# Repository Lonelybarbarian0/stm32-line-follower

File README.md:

# stm32-line-follower
An advanced line follower based on STM32F446RE. This design consists of 12 Analog IR sensors (CNY70) , a dual H-bridge driver (TB6612FNG) , has I2C ports for oled display , push buttons , 12V battery accomodation , SWD , and debug UART ports for programming and debugging the microcontroller.
Has two voltage regulators for 3V3 and 5V.

It has mounting holes for caster wheel (15mm) , specifically this one: https://robu.in/product/mini-3pi-car-n20-caster-robot-ball-wheel/?gad_source=1&gad_campaignid=20387462343&gbraid=0AAAAADvLFWdYTelDnTxbAqraLI1H4bepI&gclid=Cj0KCQjwm93DBhD_ARIsADR_DjHucWRJYjZKFOhlfUYJuclHHiB9VbRIZePeRFHvk6mzUTXiPl632kYaAhp5EALw_wcB

It also has mounting holes for adding both N20 (18mm) as well as 14mm * 16mm motor brackets like:https://roboticsdna.in/product/25mm-dc-gear-motor-block-l-shape-motor-bracket/?src=google&kwd=&adgroup={adgroup}&device=c&campaign={campaign}&adgroup={adgroup}&keyword=&matchtype=&gad_source=1&gad_campaignid=22793537991&gbraid=0AAAAAC-xzeH1j9IDTkCSxU-zOjWUDu6ZW&gclid=Cj0KCQjwm93DBhD_ARIsADR_DjG1hGDh40R1bVBjp1YW7XD5IBcDVYip5r4QT6sreYXs5M1MaoTtmnkaAhj5EALw_wcB

Features power on led , a power on switch etc...

SIDE VIEW:

BACK VIEW:

PIN CONFIG:

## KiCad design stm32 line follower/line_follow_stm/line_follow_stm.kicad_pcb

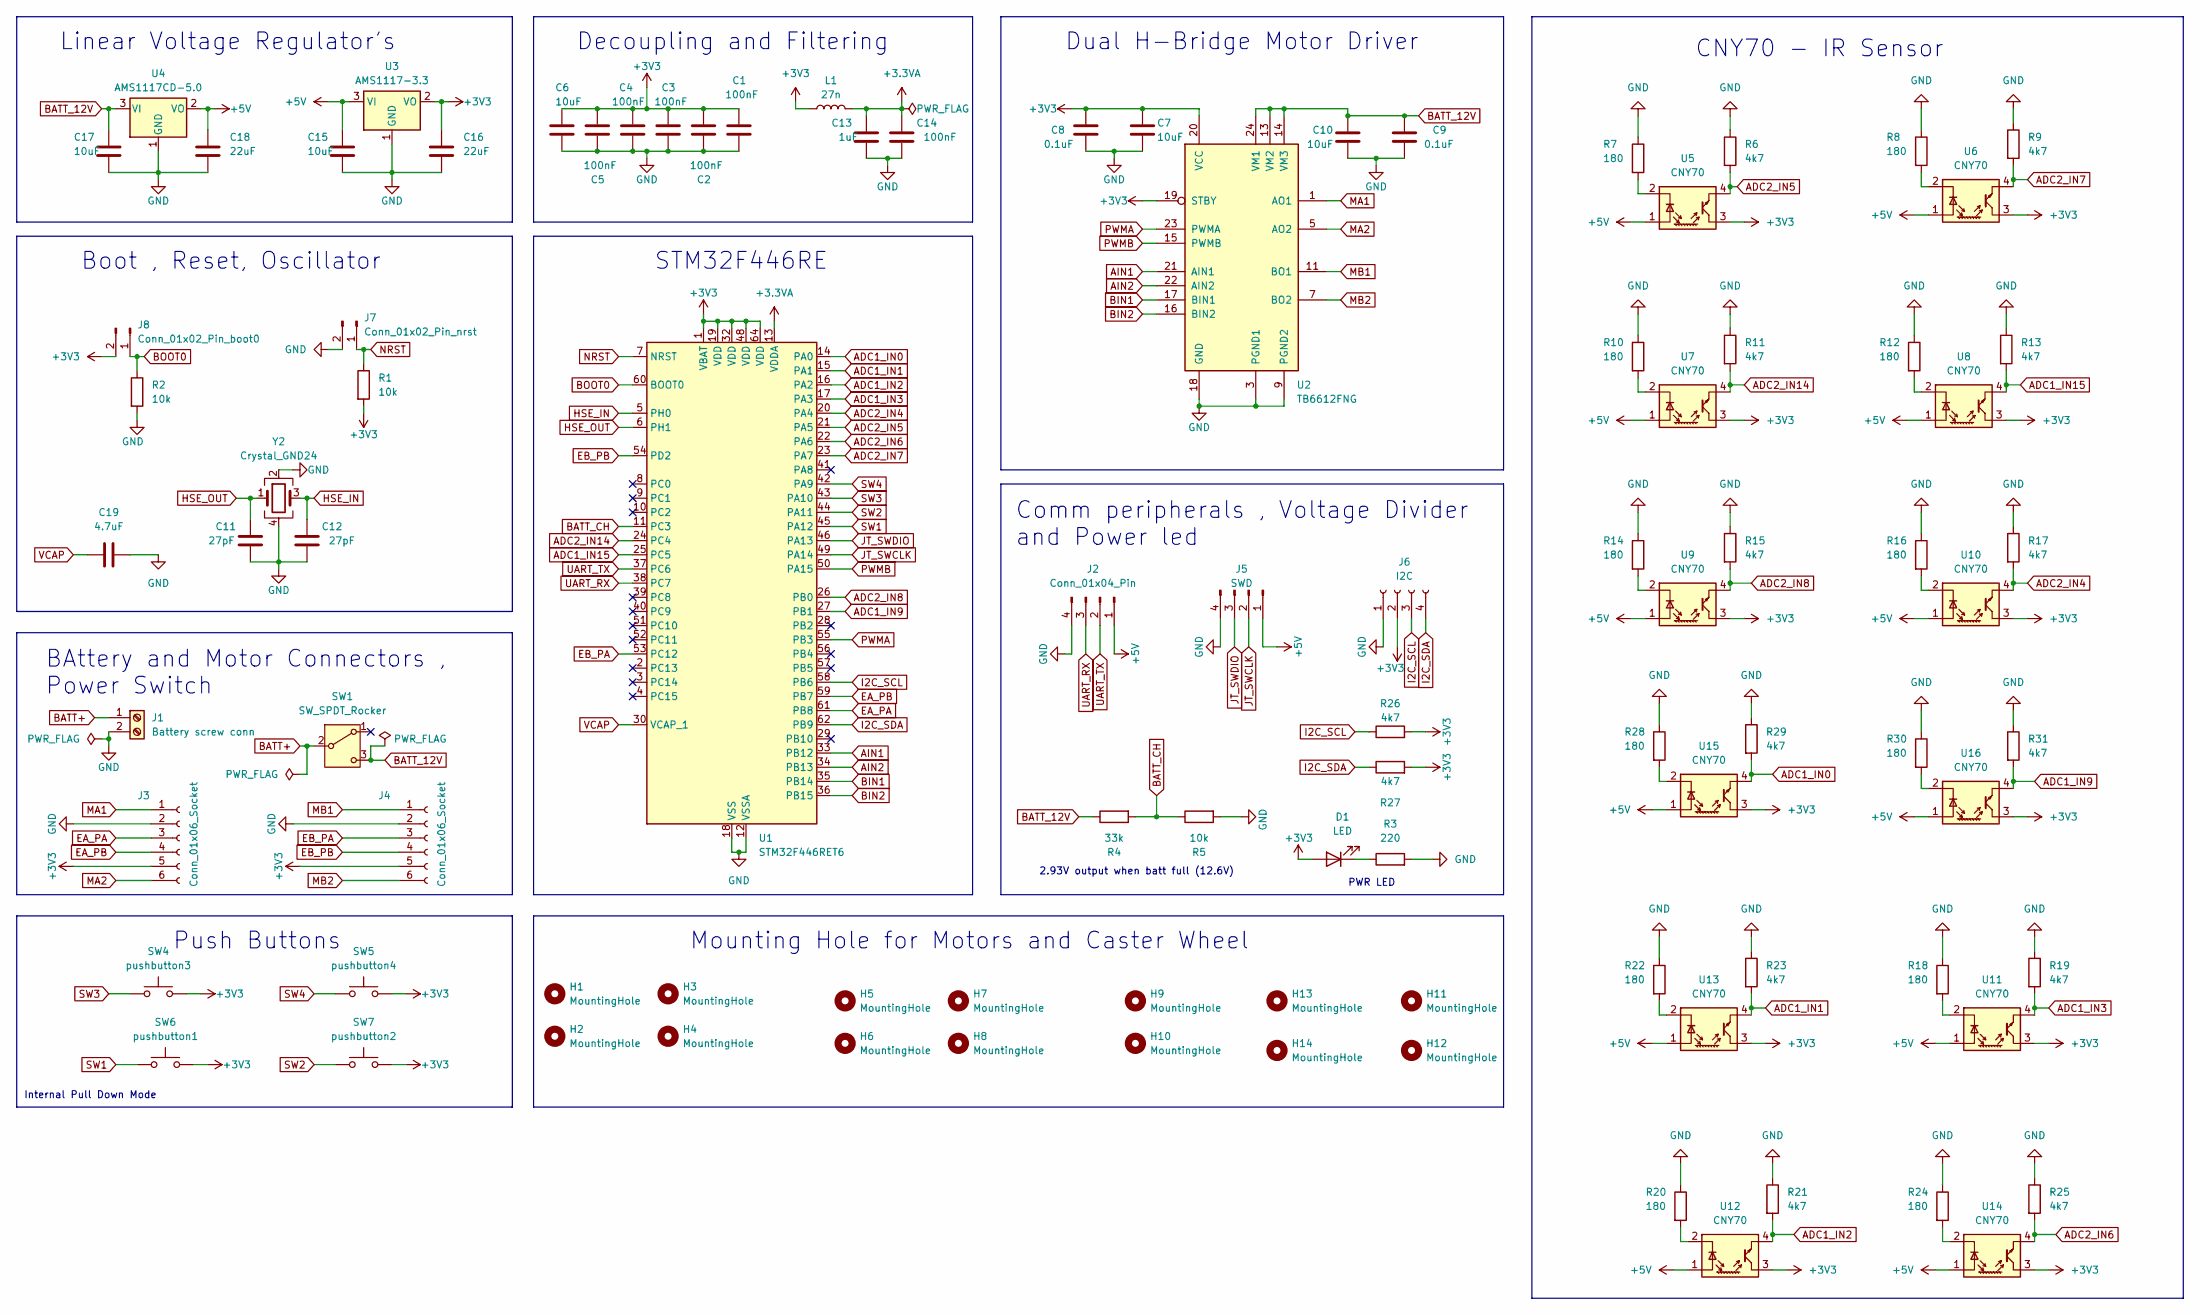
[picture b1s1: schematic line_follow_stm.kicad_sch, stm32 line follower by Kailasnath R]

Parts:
C1, C2, C4, C5, C14: 100nF; C_0805_2012Metric
C3: 100nF; C_0805_2012Metric_Pad1.18x1.45mm_HandSolder
C6, C7, C10: 10uF; C_1206_3216Metric
C8, C9: 0.1uF; C_0805_2012Metric
C11: 27pF; C_0805_2012Metric
C12: 27pF; C_0805_2012Metric_Pad1.18x1.45mm_HandSolder
C13: 1uF; C_0805_2012Metric
C15: 10uF; C_0805_2012Metric
C16: 22uF; C_1206_3216Metric_Pad1.33x1.80mm_HandSolder
C17: 10uF; C_1206_3216Metric_Pad1.33x1.80mm_HandSolder
C18: 22uF; C_1206_3216Metric
C19: 4.7uF; C_1206_3216Metric
D1: LED; LED_2010_5025Metric
H1, H2, H3, H4, H5, H6, H7, H8: MountingHole; MountingHole_3.2mm_M3
H9, H10, H11, H12, H13, H14: MountingHole; MountingHole_2.2mm_M2
J1: Battery screw conn; TE_282837-2
J2: Conn_01x04_Pin; PinSocket_1x04_P2.54mm_Vertical
J3, J4: Conn_01x06_Socket; PinSocket_1x06_P2.54mm_Vertical
J5: SWD; PinHeader_1x04_P2.54mm_Vertical
J6: I2C; PinSocket_1x04_P2.54mm_Vertical
J7: Conn_01x02_Pin_nrst; PinHeader_1x02_P2.54mm_Vertical
J8: Conn_01x02_Pin_boot0; PinHeader_1x02_P2.54mm_Vertical
L1: 27n; L_0805_2012Metric
R1, R2, R5: 10k; R_0603_1608Metric
R3: 220; R_0603_1608Metric
R4: 33k; R_0603_1608Metric
R6, R9, R11, R13, R15, R17, R19, R21, R23, R25, R26, R27, R29, R31: 4k7; R_0603_1608Metric
R7, R8, R10, R12, R14, R16, R18, R20, R22, R24, R28, R30: 180; R_0603_1608Metric
SW1: SW_SPDT_Rocker; SW_100SP1T1B4M2QE
SW4: pushbutton3; SW_PUSH-12mm_Wuerth-430476085716
SW5: pushbutton4; SW_PUSH-12mm_Wuerth-430476085716
SW6: pushbutton1; SW_PUSH-12mm_Wuerth-430476085716
SW7: pushbutton2; SW_PUSH-12mm_Wuerth-430476085716
U1: STM32F446RET6; LQFP-64_10x10mm_P0.5mm
U2: TB6612FNG; SSOP-24_5.3x8.2mm_P0.65mm
U3: AMS1117-3.3; SOT-223-3_TabPin2
U4: AMS1117CD-5.0; TO-252-3_TabPin2
U5, U6, U7, U8, U9, U10, U11, U12, U13, U14, U15, U16: CNY70; Vishay_CNY70
Y2: Crystal_GND24; XTAL_C3E-8.000-18-1020-X-R

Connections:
+3.3VA: C13.1, C14.1, L1.2, U1.13 (VDDA)
+3V3: C1.1, C2.1, C3.1, C4.1, C5.1, C6.1, C7.1, C8.1, C16.1, D1.2 (A), J3.5, J4.5, J6.2, J8.2, L1.1, R1.2, R26.2, R27.2, SW4.2, SW5.2, SW6.2, SW7.2, U1.1 (VBAT), U1.19 (VDD), U1.32 (VDD), U1.48 (VDD), U1.64 (VDD), U2.19 (STBY), U2.20 (VCC), U3.2 (VO), U5.3 (C), U6.3 (C), U7.3 (C), U8.3 (C), U9.3 (C), U10.3 (C), U11.3 (C), U12.3 (C), U13.3 (C), U14.3 (C), U15.3 (C), U16.3 (C)
+5V: C15.1, C18.1, J2.1, J5.1, U3.3 (VI), U4.2 (VO), U5.1 (A), U6.1 (A), U7.1 (A), U8.1 (A), U9.1 (A), U10.1 (A), U11.1 (A), U12.1 (A), U13.1 (A), U14.1 (A), U15.1 (A), U16.1 (A)
ADC1_IN0: R29.2, U1.14 (PA0), U15.4 (E)
ADC1_IN1: R23.2, U1.15 (PA1), U13.4 (E)
ADC1_IN2: R21.2, U1.16 (PA2), U12.4 (E)
ADC1_IN3: R19.2, U1.17 (PA3), U11.4 (E)
ADC1_IN9: R31.2, U1.27 (PB1), U16.4 (E)
ADC1_IN15: R13.2, U1.25 (PC5), U8.4 (E)
ADC2_IN4: R17.2, U1.20 (PA4), U10.4 (E)
ADC2_IN5: R6.2, U1.21 (PA5), U5.4 (E)
ADC2_IN6: R25.2, U1.22 (PA6), U14.4 (E)
ADC2_IN7: R9.2, U1.23 (PA7), U6.4 (E)
ADC2_IN8: R15.2, U1.26 (PB0), U9.4 (E)
ADC2_IN14: R11.2, U1.24 (PC4), U7.4 (E)
AIN1: U1.33 (PB12), U2.21 (AIN1)
AIN2: U1.34 (PB13), U2.22 (AIN2)
BATT+: J1.1, SW1.2 (B)
BATT_12V: C9.1, C10.1, C17.1, R4.1, SW1.3 (C), U2.13 (VM2), U2.14 (VM3), U2.24 (VM1), U4.3 (VI)
BATT_CH: R4.2, R5.1, U1.11 (PC3)
BIN1: U1.35 (PB14), U2.17 (BIN1)
BIN2: U1.36 (PB15), U2.16 (BIN2)
BOOT0: J8.1, R2.1, U1.60 (BOOT0)
EA_PA: J3.3, U1.61 (PB8)
EA_PB: J3.4, U1.59 (PB7)
EB_PA: J4.3, U1.53 (PC12)
EB_PB: J4.4, U1.54 (PD2)
GND: C1.2, C2.2, C3.2, C4.2, C5.2, C6.2, C7.2, C8.2, C9.2, C10.2, C11.2, C12.2, C13.2, C14.2, C15.2, C16.2, C17.2, C18.2, C19.2, J1.2, J2.4, J3.2, J4.2, J5.4, J6.1, J7.2, R2.2, R3.2, R5.2, R6.1, R7.1, R8.1, R9.1, R10.1, R11.1, R12.1, R13.1, R14.1, R15.1, R16.1, R17.1, R18.1, R19.1, R20.1, R21.1, R22.1, R23.1, R24.1, R25.1, R28.1, R29.1, R30.1, R31.1, U1.12 (VSSA), U1.18 (VSS), U1.31 (VSS), U1.47 (VSS), U1.63 (VSS), U2.3 (PGND1), U2.4 (PGND1), U2.9 (PGND2), U2.10 (PGND2), U2.18 (GND), U3.1 (GND), U4.1 (GND), Y2.2, Y2.4
HSE_IN: C12.1, U1.5 (PH0), Y2.3
HSE_OUT: C11.1, U1.6 (PH1), Y2.1
I2C_SCL: J6.3, R26.1, U1.58 (PB6)
I2C_SDA: J6.4, R27.1, U1.62 (PB9)
JT_SWCLK: J5.2, U1.49 (PA14)
JT_SWDIO: J5.3, U1.46 (PA13)
MA1: J3.1, U2.1 (AO1), U2.2 (AO1)
MA2: J3.6, U2.5 (AO2), U2.6 (AO2)
MB1: J4.1, U2.11 (BO1), U2.12 (BO1)
MB2: J4.6, U2.7 (BO2), U2.8 (BO2)
NRST: J7.1, R1.1, U1.7 (NRST)
unnamed: D1.1 (K), R3.1
unnamed: R7.2, U5.2 (K)
unnamed: R8.2, U6.2 (K)
unnamed: R10.2, U7.2 (K)
unnamed: R12.2, U8.2 (K)
unnamed: R14.2, U9.2 (K)
unnamed: R16.2, U10.2 (K)
unnamed: R18.2, U11.2 (K)
unnamed: R20.2, U12.2 (K)
unnamed: R22.2, U13.2 (K)
unnamed: R24.2, U14.2 (K)
unnamed: R28.2, U15.2 (K)
unnamed: R30.2, U16.2 (K)
PWMA: U1.55 (PB3), U2.23 (PWMA)
PWMB: U1.50 (PA15), U2.15 (PWMB)
SW1: SW6.1, U1.45 (PA12)
SW2: SW7.1, U1.44 (PA11)
SW3: SW4.1, U1.43 (PA10)
SW4: SW5.1, U1.42 (PA9)
UART_RX: J2.3, U1.38 (PC7)
UART_TX: J2.2, U1.37 (PC6)
VCAP: C19.1, U1.30 (VCAP_1)

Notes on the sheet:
CNY70 - IR Sensor
Linear Voltage Regulator's
BAttery and Motor Connectors , Power Switch
STM32F446RE
Comm peripherals , Voltage Divider and Power led
Dual H-Bridge Motor Driver
Decoupling and Filtering
Internal Pull Down Mode
2.93V output when batt full (12.6V)
Mounting Hole for Motors and Caster Wheel
Boot , Reset, Oscillator
PWR LED
Push Buttons

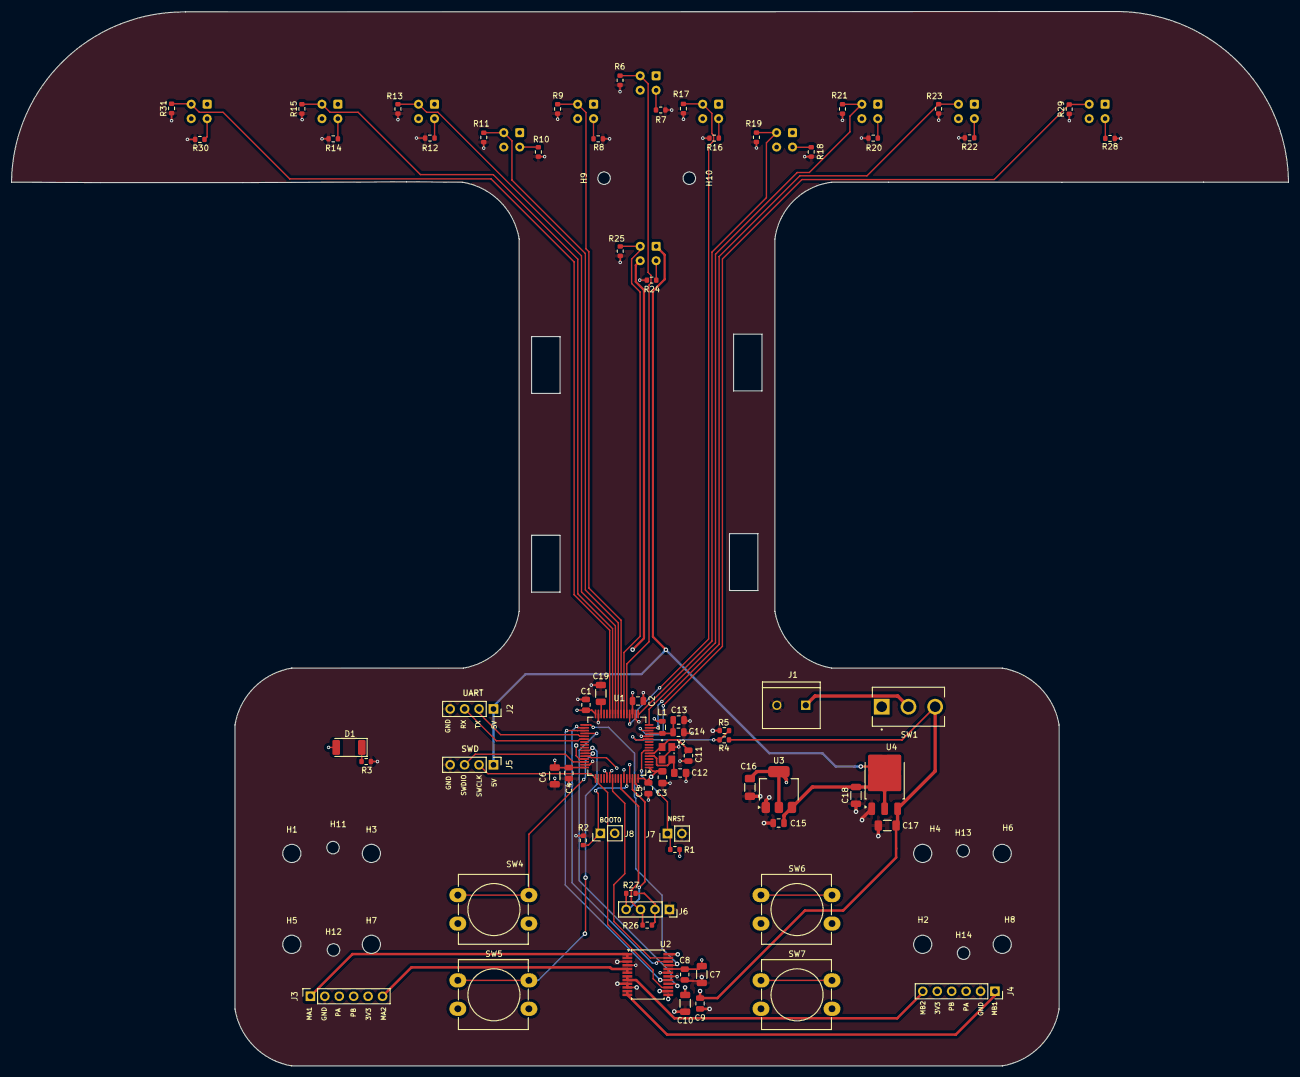
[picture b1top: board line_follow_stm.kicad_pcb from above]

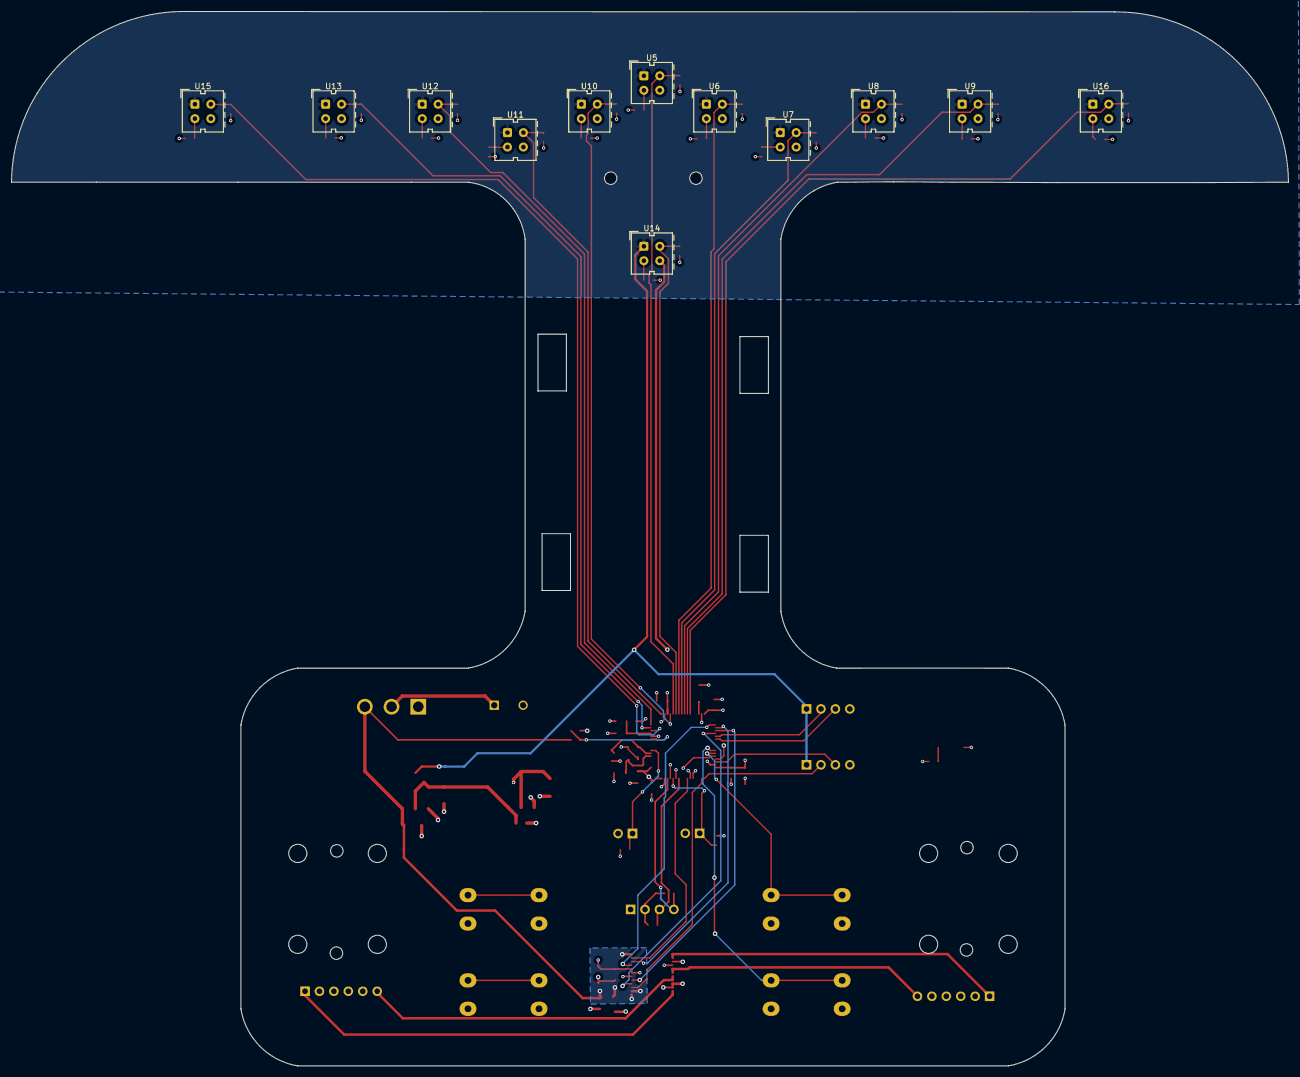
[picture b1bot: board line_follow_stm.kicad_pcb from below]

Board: 4 copper layers, 224.7 x 185.5 mm, 96 parts (12 on the bottom side), 61 nets.

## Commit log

2025-07-16 V 1.0
    First Version
2025-07-16 stm32 line follower
    V 1.0
